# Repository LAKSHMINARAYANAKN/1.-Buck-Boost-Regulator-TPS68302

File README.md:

# 1.-Buck-Boost-Regulator-TPS68302
A buck boost regulator with Input range from 2.3-5.5V(Battery input) and outputs 3.3/3.8/adj @2.5A

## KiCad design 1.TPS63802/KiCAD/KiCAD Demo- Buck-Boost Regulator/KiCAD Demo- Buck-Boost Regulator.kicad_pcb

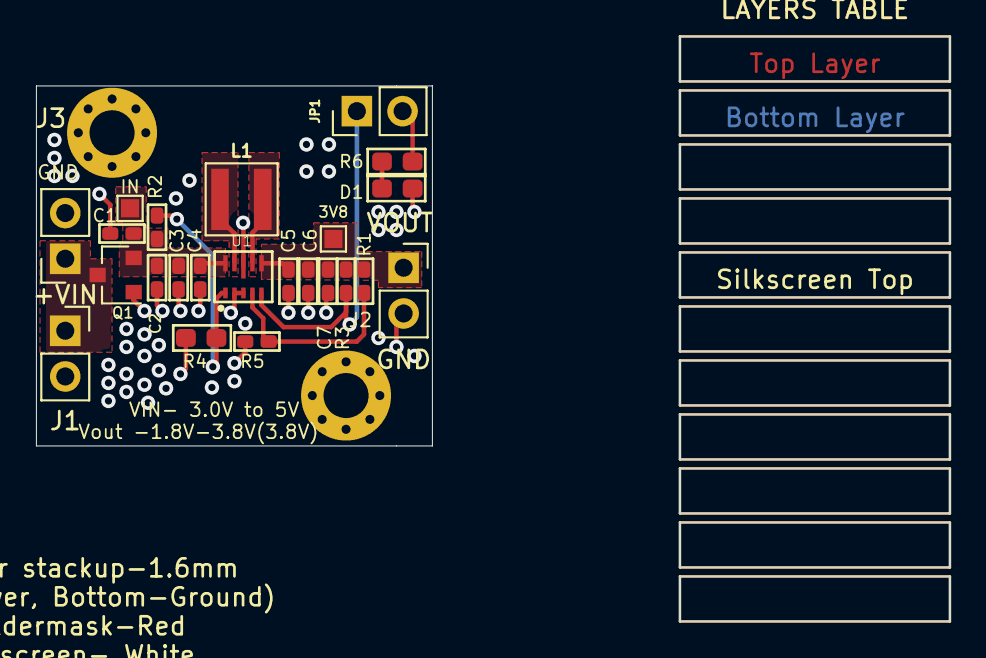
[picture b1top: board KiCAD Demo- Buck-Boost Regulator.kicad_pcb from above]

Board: 2 copper layers, 50.8 x 32.5 mm, 25 parts (0 on the bottom side), 11 nets.

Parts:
3V8: 3V8; TestPoint_Pad_1.0x1.0mm
C1, C4, C7: 0u1F; C0402
C2, C3, C5, C6: 22uF; C0402
D1: RLED; D0603
H1, H2: MH; MountingHole_2.5mm_Pad_Via
IN: VIN; TestPoint_Pad_1.0x1.0mm
J1: Battery I/P; PinSocket_1x02_P2.54mm_Vertical
J2: OUT; PinSocket_1x02_P2.54mm_Vertical
J3: External I/P; PinSocket_1x02_P2.54mm_Vertical
JP1: Jumper; PinHeader_1x02_P2.54mm_Vertical
L1: 1.5uH 11.2A; XFL401571MEB
Q1: Si2319CDS; SOT-23
R1: 1M; R0402
R2: 82K5; R0402
R3: 600K; R0402
R4: 49K9; R0603
R5: 91K; R0402
R6: 180; R0603
U1: U1; TPS63802

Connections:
+VIN: C1.1, C2.1, C3.1, C4.1, IN.1, Q1.2, R2.2, U1.10
+VOUT: 3V8.1, C5.1, C6.1, C7.1, J2.1, R1.1, R3.2, U1.6
/Power /+VBAT: J1.1, J3.1, Q1.3
/Power /PG: JP1.1, R1.2, U1.5
GND: C1.2, C2.2, C3.2, C4.2, C5.2, C6.2, C7.2, D1.1, J1.2, J2.2, J3.2, Q1.1, R4.1, R5.1, U1.2, U1.3, U1.8
unnamed: D1.2, R6.2
unnamed: JP1.2, R6.1
unnamed: L1.1, U1.9
unnamed: L1.2, U1.7
unnamed: R2.1, R4.2, U1.1
unnamed: R3.1, R5.2, U1.4

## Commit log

2020-07-26 Added KiCAD Files, step model
